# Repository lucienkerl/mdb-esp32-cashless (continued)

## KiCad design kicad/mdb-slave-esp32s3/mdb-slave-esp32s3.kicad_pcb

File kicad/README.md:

# MDB ESP32 Cashless Devices

This repository contains open hardware projects for MDB-based cashless devices built around the ESP32 platform.

## PCBWay Project Store
You can view and order the PCBs directly from PCBWay using the links below:

👉 MDB ESP32-S3-WROOM-1U board: https://www.pcbway.com/project/shareproject/MDB_Slave_ESP32_S3_WROOM_1U_4_layer_cashless_telemetry_board_for_vending_mac_cb2e3ef8.html

👉 Other boards: https://www.pcbway.com/project/member/?bmbno=1B3B95CB-4E28-4D

---

### MDB ESP32-S3-WROOM-1U Cashless Device

4-layer board with external antenna, relays and sensor I/O — see [`mdb_slave_esp32s3-wroom-1u/`](mdb_slave_esp32s3-wroom-1u/) for sources, gerbers and the interactive BOM.

### LTE add-on module (SIM7080G) for the WROOM-1U board

Plugs into the WROOM-1U board's J2 socket and adds LTE-M / NB-IoT — see [`lte-addon-sim7080g/`](lte-addon-sim7080g/).

### MDB ESP32 Cashless Device

### MDB ESP32 GPS/LTE-M/NB-IoT Cashless Device

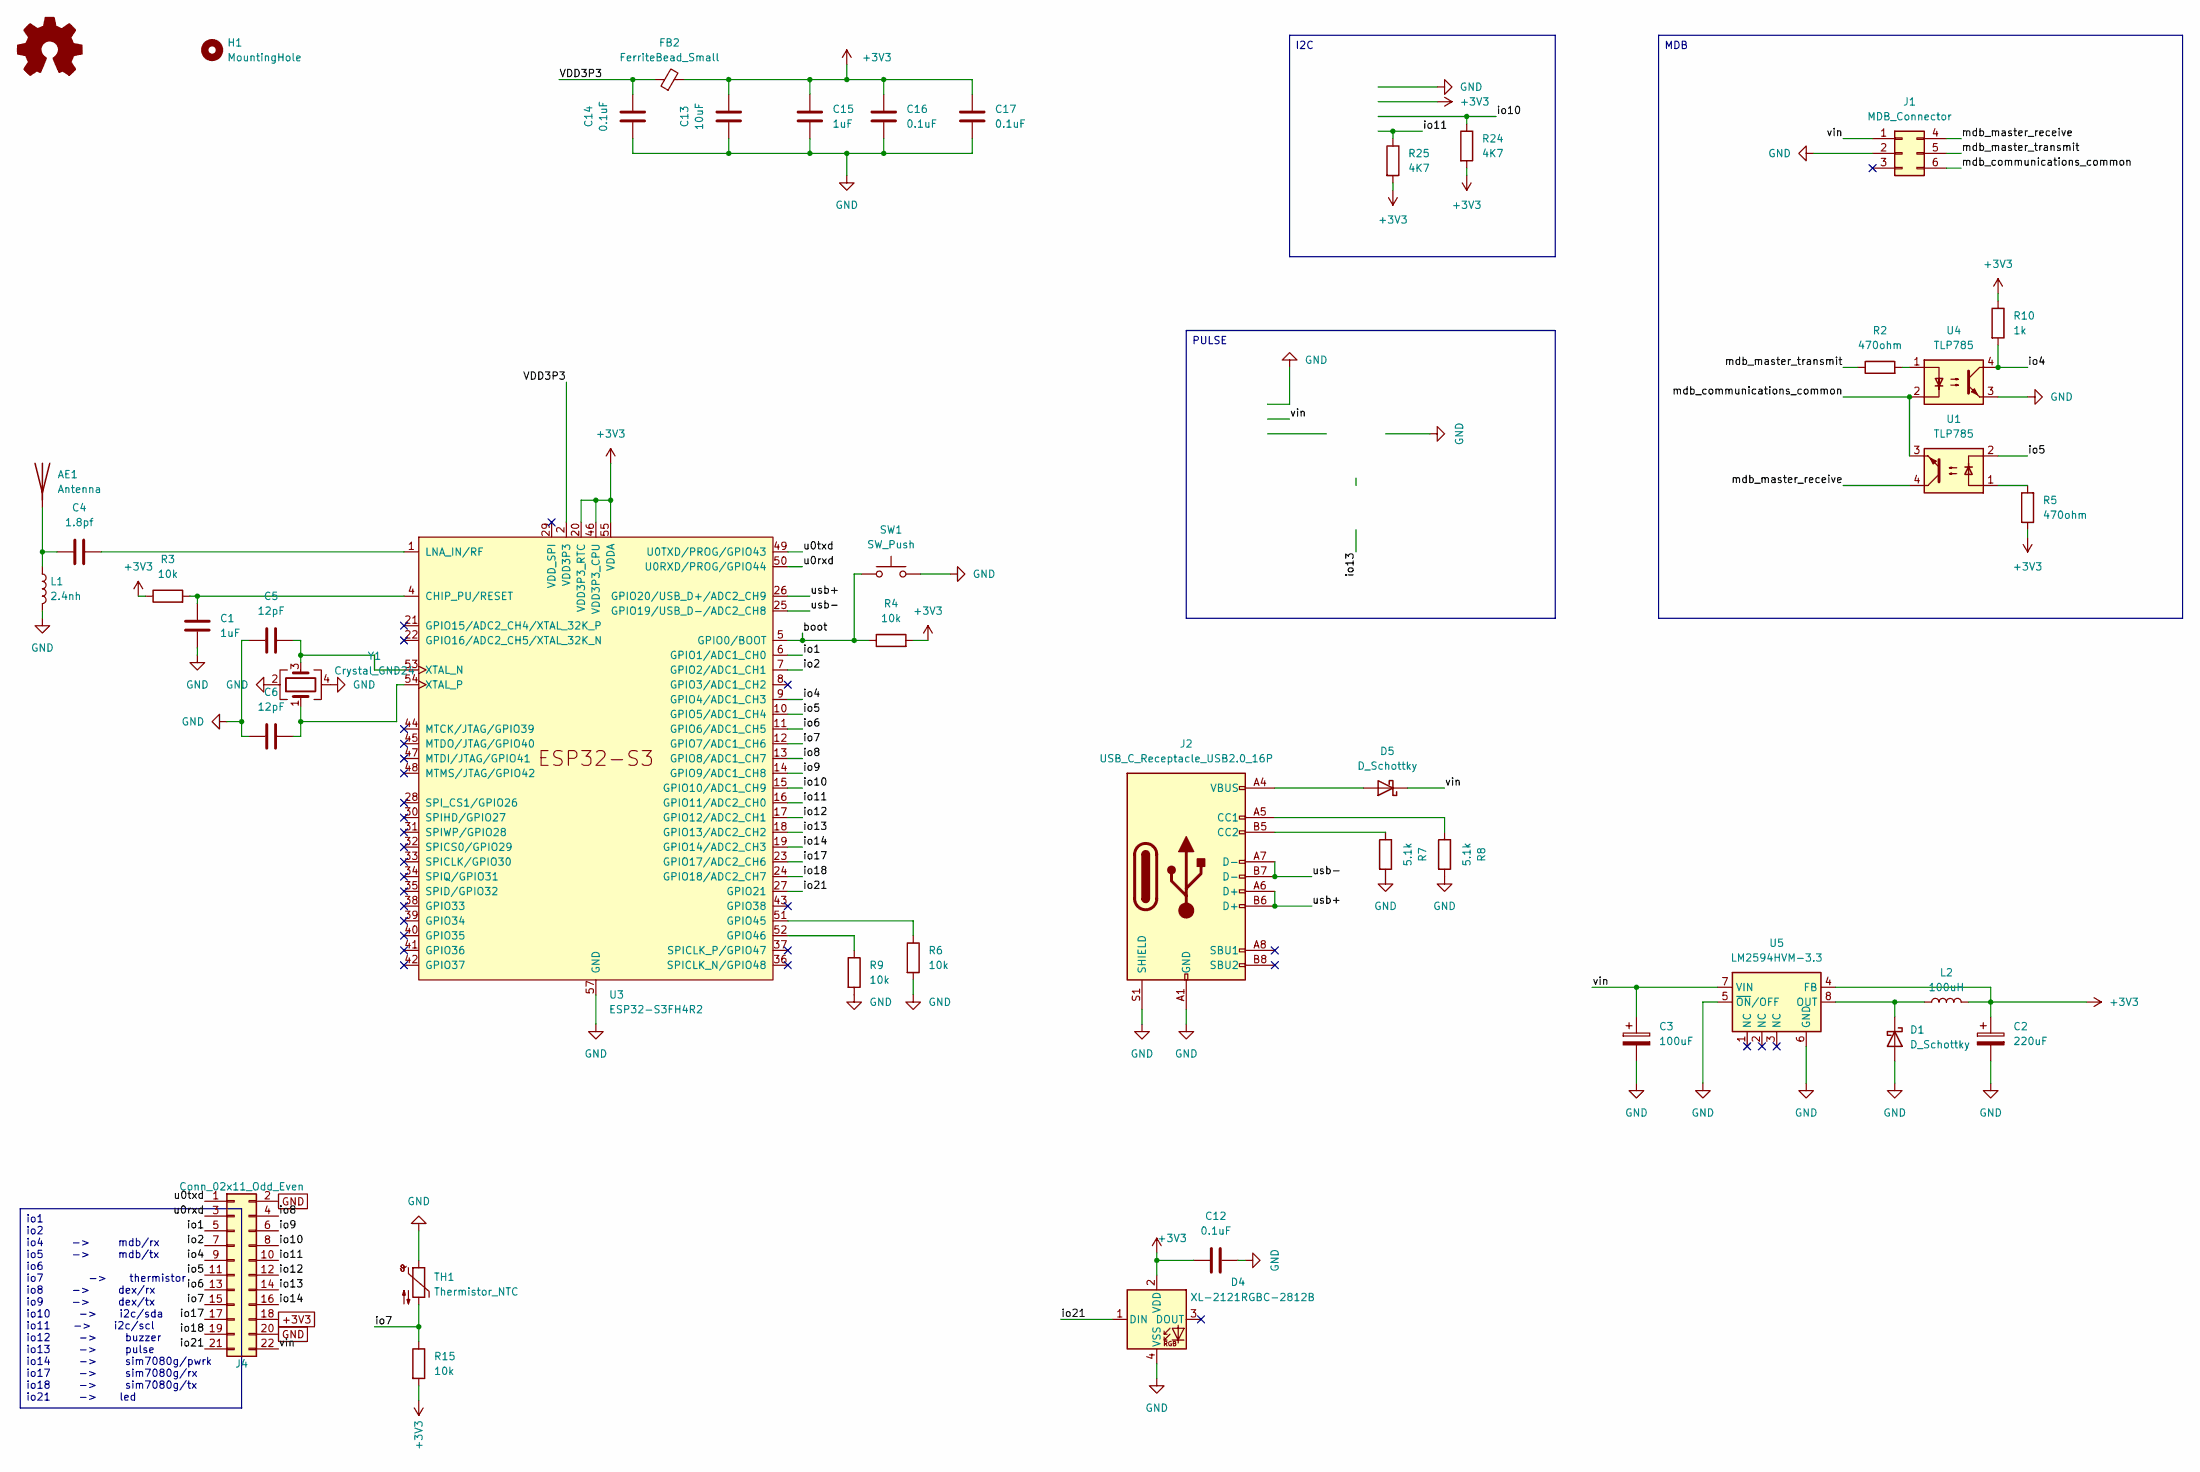
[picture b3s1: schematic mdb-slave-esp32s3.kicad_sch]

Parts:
AE1: Antenna; Texas_SWRA117D_2.4GHz_Left
C1, C15: 1uF; C_0603_1608Metric; LCSC# C6119849
C2: 220uF; CP_EIA-3528-21_Kemet-B; LCSC# C30242
C3: 100uF; CP_Elec_6.3x5.8; LCSC# C128464
C4: 1.8pf; C_0603_1608Metric; LCSC# C376773
C5, C6: 12pF; C_0603_1608Metric; LCSC# C363546
C12, C14, C16, C17: 0.1uF; C_0603_1608Metric; LCSC# C5137636
C13: 10uF; C_0603_1608Metric; LCSC# C6119864
D1, D5: D_Schottky; D_SOD-123; LCSC# C18195164
D4: XL-2121RGBC-2812B; LED_WS2812B-2020_PLCC4_2.0x2.0mm; LCSC# C5349957
FB2: FerriteBead_Small; L_0603_1608Metric; LCSC# C304319
H1: MountingHole; MountingHole_2.1mm
J1: MDB_Connector; Molex_Mini-Fit_Jr_5566-06A_2x03_P4.20mm_Vertical; LCSC# C22365701
J2: USB_C_Receptacle_USB2.0_16P; USB_C_Receptacle_G-Switch_GT-USB-7010ASV; LCSC# C2988369
J4: Conn_02x11_Odd_Even; PinHeader_2x11_P2.54mm_Vertical
L1: 2.4nh; L_0603_1608Metric; LCSC# C2042508
L2: 100uH; L_7.3x7.3_H3.5; LCSC# C182195
R2, R5: 470ohm; R_0603_1608Metric; LCSC# C114669
R3, R4, R6, R9, R15: 10k; R_0603_1608Metric; LCSC# C98220
R7, R8: 5.1k; R_0603_1608Metric; LCSC# C394543
R10: 1k; R_0603_1608Metric; LCSC# C2907113
R24, R25: 4K7; R_0603_1608Metric; LCSC# C23162
SW1: SW_Push; SW_Tactile_SPST_NO_Straight_CK_PTS636Sx25SMTRLFS; LCSC# C42435421
TH1: Thermistor_NTC; R_0603_1608Metric; LCSC# C13564
U1, U4: TLP785; SOP-4_3.8x4.1mm_P2.54mm; LCSC# C128776
U3: ESP32-S3FH4R2; QFN-56-1EP_7x7mm_P0.4mm_EP4x4mm; LCSC# C3013940
U5: LM2594HVM-3.3; SOIC-8_3.9x4.9mm_P1.27mm; LCSC# C18057294
Y1: Crystal_GND24; Crystal_SMD_3225-4Pin_3.2x2.5mm; LCSC# C7294599

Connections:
+3V3: C2.1, C12.2, C13.2, C15.2, C16.1, C17.1, D4.2 (VDD), FB2.2, J4.18, L2.2, R3.1, R4.2, R5.1, R10.1, R15.2, R24.2, R25.2, U3.20 (VDD3P3_RTC), U3.46 (VDD3P3_CPU), U3.55 (VDDA), U3.56 (VDDA), U5.4 (FB)
/boot: R4.1, SW1.1, U3.5 (GPIO0/BOOT)
/io1: J4.5, U3.6 (GPIO1/ADC1_CH0)
/io2: J4.7, U3.7 (GPIO2/ADC1_CH1)
/io4: J4.9, R10.2, U3.9 (GPIO4/ADC1_CH3), U4.4
/io5: J4.11, U1.2, U3.10 (GPIO5/ADC1_CH4)
/io6: J4.13, U3.11 (GPIO6/ADC1_CH5)
/io7: J4.15, R15.1, TH1.2, U3.12 (GPIO7/ADC1_CH6)
/io8: J4.4, U3.13 (GPIO8/ADC1_CH7)
/io9: J4.6, U3.14 (GPIO9/ADC1_CH8)
/io10: J4.8, R24.1, U3.15 (GPIO10/ADC1_CH9)
/io11: J4.10, R25.1, U3.16 (GPIO11/ADC2_CH0)
/io12: J4.12, U3.17 (GPIO12/ADC2_CH1)
/io13: J4.14, U3.18 (GPIO13/ADC2_CH2)
/io14: J4.16, U3.19 (GPIO14/ADC2_CH3)
/io17: J4.17, U3.23 (GPIO17/ADC2_CH6)
/io18: J4.19, U3.24 (GPIO18/ADC2_CH7)
/io21: D4.1 (DIN), J4.21, U3.27 (GPIO21)
/mdb_communications_common: J1.6, U1.3, U4.2
/mdb_master_receive: J1.4, U1.4
/mdb_master_transmit: J1.5, R2.1
/u0rxd: J4.3, U3.50 (U0RXD/PROG/GPIO44)
/u0txd: J4.1, U3.49 (U0TXD/PROG/GPIO43)
/usb+: J2.A6 (D+), J2.B6 (D+), U3.26 (GPIO20/USB_D+/ADC2_CH9)
/usb-: J2.A7 (D-), J2.B7 (D-), U3.25 (GPIO19/USB_D-/ADC2_CH8)
/vin: C3.1, D5.1 (K), J1.1, J4.22, U5.7 (VIN)
GND: C1.2, C2.2, C3.2, C5.1, C6.1, C12.1, C13.1, C14.1, C15.1, C16.2, C17.2, D1.2 (A), D4.4 (VSS), J1.2, J2.A1 (GND), J2.A12 (GND), J2.B1 (GND), J2.B12 (GND), J2.S1 (SHIELD), J4.2, J4.20, L1.2, R6.2, R7.2, R8.2, R9.2, SW1.2, TH1.1, U3.57 (GND), U4.3, U5.5 (~ON/OFF), U5.6 (GND), Y1.2, Y1.4
unnamed: AE1.1 (A_1), C4.1, L1.1
unnamed: D1.1 (K), L2.1, U5.8 (OUT)
unnamed: D5.2 (A), J2.A4 (VBUS), J2.A9 (VBUS), J2.B4 (VBUS), J2.B9 (VBUS)
unnamed: J2.A5 (CC1), R8.1
unnamed: J2.B5 (CC2), R7.1
unnamed: R2.2, U4.1
unnamed: R5.2, U1.1
unnamed: C1.1, R3.2, U3.4 (CHIP_PU/RESET)
unnamed: R6.1, U3.51 (GPIO45)
unnamed: R9.1, U3.52 (GPIO46)
unnamed: C4.2, U3.1 (LNA_IN/RF)
unnamed: C5.2, U3.53 (XTAL_N), Y1.3
unnamed: C6.2, U3.54 (XTAL_P), Y1.1
VDD3P3: C14.2, FB2.1, U3.2 (VDD3P3), U3.3 (VDD3P3)

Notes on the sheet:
io1 io2 io4 -> mdb/rx io5 -> mdb/tx io6 io7 -> thermistor io8 -> dex/rx io9 -> dex/tx io10 -> i2c/sda io11 -> i2c/scl io12 -> buzzer io13 -> pulse io14 -> sim7080g/pwrk io17 -> sim7080g/rx io18 -> sim7080g/tx io21 -> led
PULSE
I2C
MDB

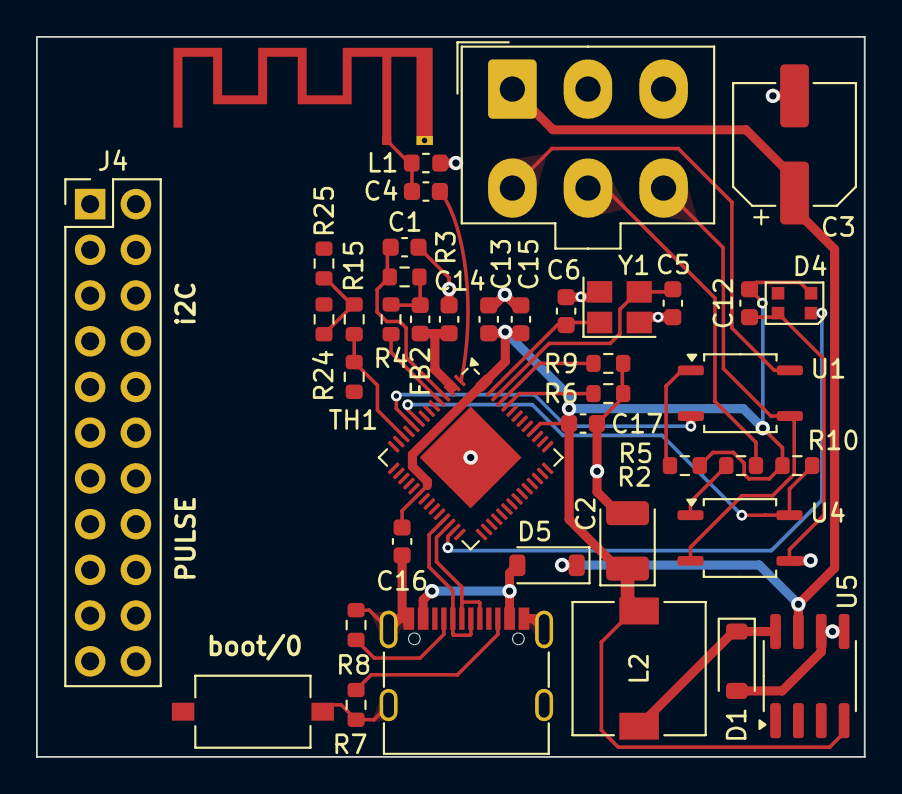
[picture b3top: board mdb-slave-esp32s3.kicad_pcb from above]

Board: 2 copper layers, 46.0 x 40.0 mm, 41 parts (0 on the bottom side), 41 nets.

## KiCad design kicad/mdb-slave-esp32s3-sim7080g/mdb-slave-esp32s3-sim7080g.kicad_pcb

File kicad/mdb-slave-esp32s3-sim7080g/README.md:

# mdb-slave-esp32s3-sim7080g — pin mapping & firmware compatibility

Custom PCB variant of `mdb-slave-esp32s3` adding an onboard SIM7080G
(GPS/LTE-M/NB-IoT) modem — see `kicad/README.md` for the board photo.

## Confirmed pin mapping (traced from `mdb-slave-esp32s3-sim7080g.kicad_pcb` netlist)

| GPIO | Net | Function |
|---|---|---|
| 4 | `/io4` | MDB bus (bridged to `/mdb_communications_common` — same role as the base board's `PIN_MDB_RX`) |
| 5 | `/io5` | MDB bus (bridged to `/mdb_communications_common` — same role as `PIN_MDB_TX`) |
| 14 | `/io14` → R (base) → Q2 | SIM7080G PWRKEY, via an inverting NPN driver (Q2: base from GPIO14 through a resistor, emitter to GND, collector to `/pwrkey`) — GPIO high → Q2 conducts → PWRKEY pulled low ("press"), same inverted-polarity convention as `MODEM_PWRKEY_INVERTED` in `modem.c` |
| 17 | `/io17` → Q1 → `/sim_uart1_rx` | ESP TX → SIM7080G UART1_RXD, via level-shift transistor Q1 |
| 18 | `/io18` → Q3 → `/sim_uart1_tx` | SIM7080G UART1_TXD → ESP RX, via level-shift transistor Q3 |

No AXP2101 (or any other PMU) is present on this board — modem power is
gated purely by the PWRKEY drive above. SIM7080G UART1 RTS/CTS/DCD/DTR/RI
are all left unconnected (2-wire UART only).

## Firmware status: supported

`main/modem.c` uses exactly this pinout by default (RX 18, TX 17, PWRKEY
14, `MODEM_PWRKEY_INVERTED` = 1) and needs no PMU. (An earlier revision of
this file described a LilyGo-devkit pinout in `modem.c`; that is gone.)

The WROOM-1U board has no modem of its own; its optional plug-in LTE module
([`../lte-addon-sim7080g/`](../lte-addon-sim7080g/)) reuses this board's
modem circuit on GPIO39/40/41 and is selected at boot via `modem_set_pins()`.

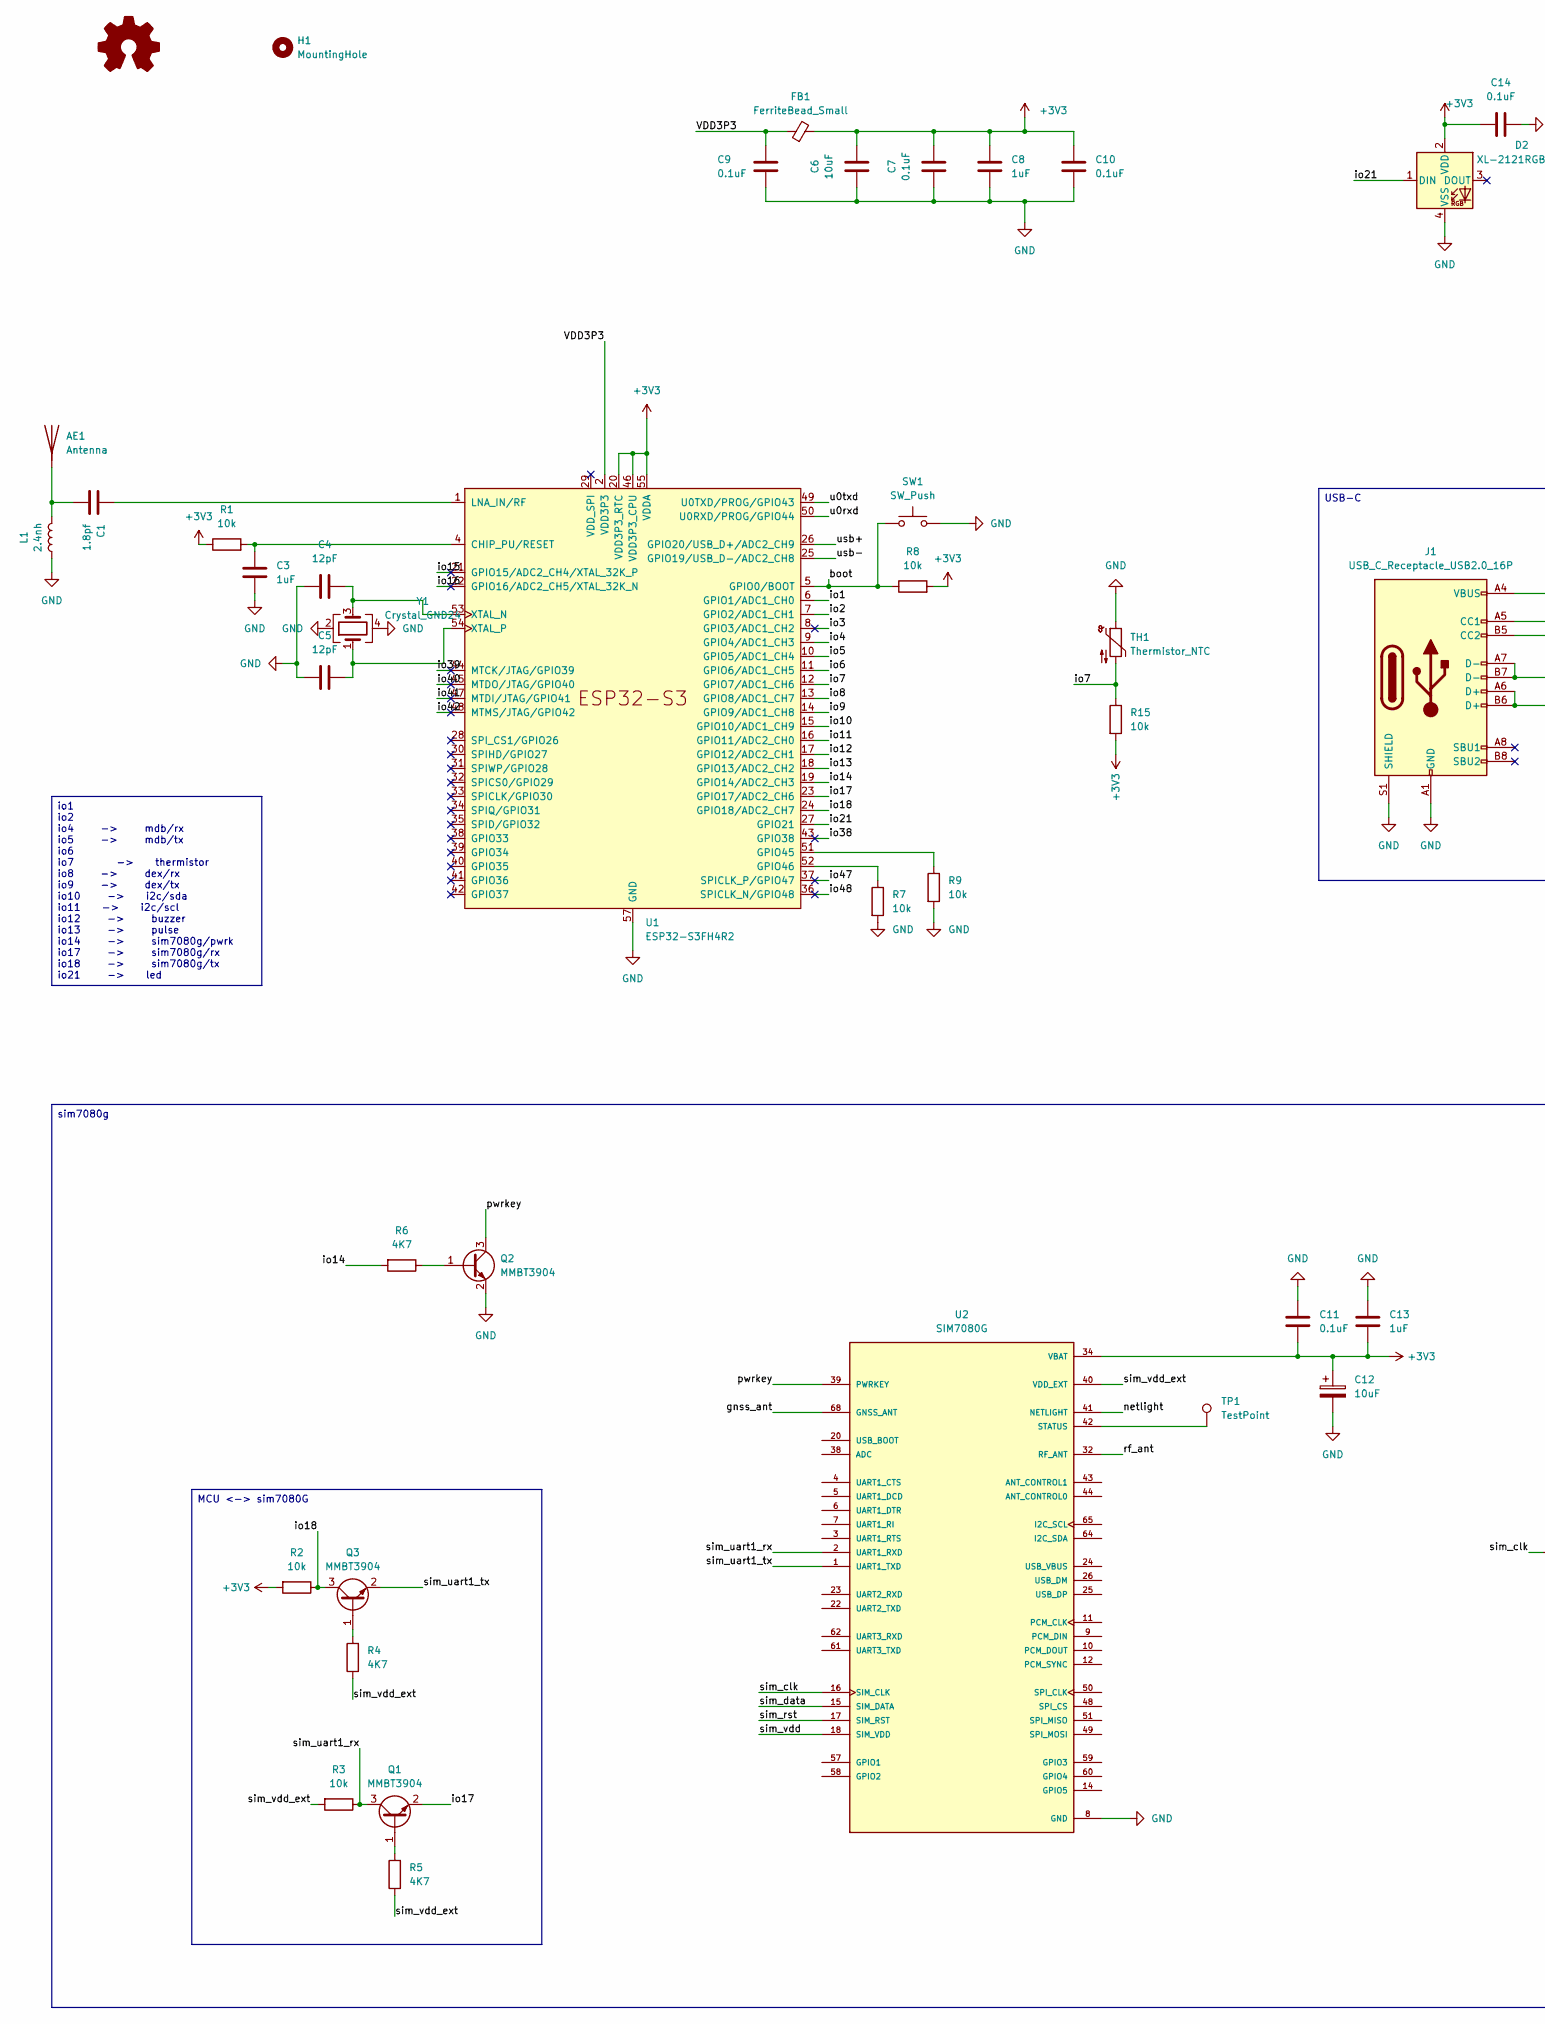
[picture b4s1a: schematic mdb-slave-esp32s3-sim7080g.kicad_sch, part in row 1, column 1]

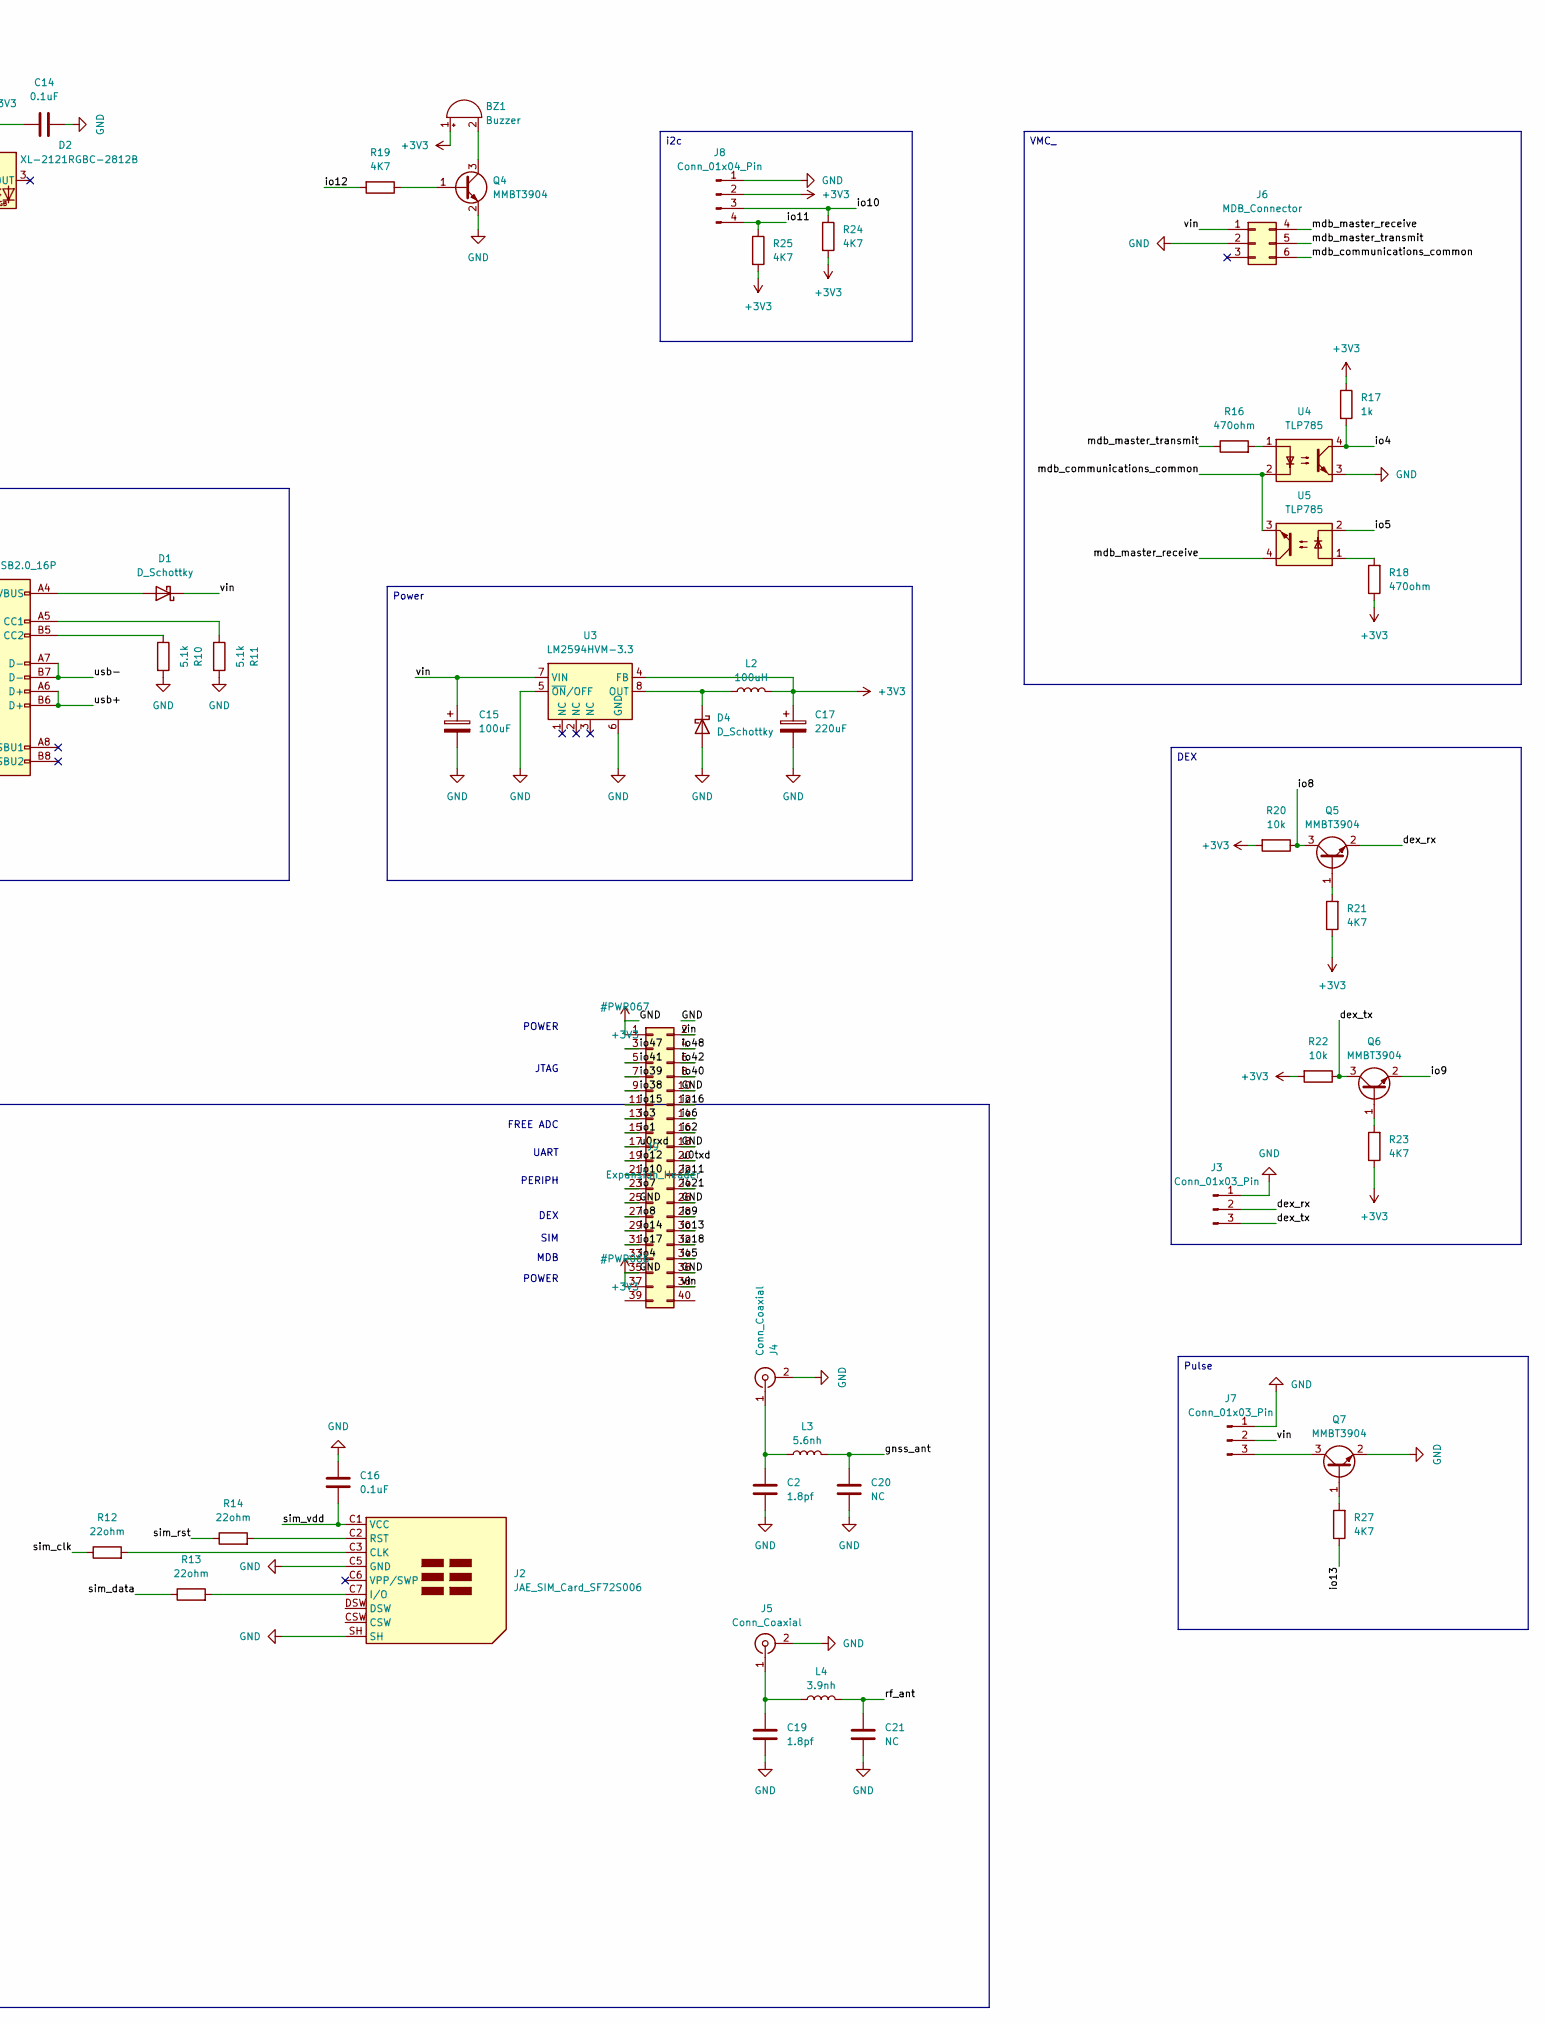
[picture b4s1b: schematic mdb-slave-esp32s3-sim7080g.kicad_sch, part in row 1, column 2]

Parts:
AE1: Antenna; Texas_SWRA117D_2.4GHz_Left
BZ1: Buzzer; Buzzer_CUI_CPT-9019S-SMT; LCSC# C255327
C1, C2, C19: 1.8pf; C_0603_1608Metric; LCSC# C376773
C3, C8, C13: 1uF; C_0603_1608Metric; LCSC# C6119849
C4, C5: 12pF; C_0603_1608Metric; LCSC# C363546
C6: 10uF; C_0603_1608Metric; LCSC# C6119864
C7, C9, C10, C11, C14, C16: 0.1uF; C_0603_1608Metric; LCSC# C5137636
C12: 10uF; CP_EIA-3528-21_Kemet-B; LCSC# C110053
C15: 100uF; CP_Elec_6.3x5.8; LCSC# C128464
C17: 220uF; CP_EIA-3528-21_Kemet-B; LCSC# C30242
C20: NC; C_0603_1608Metric; LCSC# C376773
C21: NC; C_0603_1608Metric
D1, D4: D_Schottky; D_SOD-123; LCSC# C18195164
D2: XL-2121RGBC-2812B; LED_WS2812B-2020_PLCC4_2.0x2.0mm; LCSC# C5349957
FB1: FerriteBead_Small; L_0603_1608Metric; LCSC# C304319
H1: MountingHole; MountingHole_2.1mm
J1: USB_C_Receptacle_USB2.0_16P; USB_C_Receptacle_G-Switch_GT-USB-7010ASV; LCSC# C2988369
J2: JAE_SIM_Card_SF72S006; LCSC# C2977286
J3, J7: Conn_01x03_Pin; JST_PH_B3B-PH-K_1x03_P2.00mm_Vertical; LCSC# C131339
J4, J5: Conn_Coaxial; U.FL_Hirose_U.FL-R-SMT-1_Vertical; LCSC# C88374
J6: MDB_Connector; Molex_Mini-Fit_Jr_5566-06A_2x03_P4.20mm_Vertical; LCSC# C22365701
J8: Conn_01x04_Pin; JST_PH_B4B-PH-K_1x04_P2.00mm_Vertical; LCSC# C131334
J9: Expansion_Header; PinHeader_2x20_P2.54mm_Vertical
L1: 2.4nh; L_0603_1608Metric; LCSC# C2042508
L2: 100uH; L_7.3x7.3_H3.5; LCSC# C182195
L3: 5.6nh; L_0603_1608Metric; LCSC# C6652920
L4: 3.9nh; L_0603_1608Metric; LCSC# C317982
Q1, Q2, Q3, Q4, Q5, Q6, Q7: MMBT3904; SOT-23; LCSC# C916374
R1, R2, R3, R7, R8, R9, R15, R20, R22: 10k; R_0603_1608Metric; LCSC# C98220
R4, R5, R6, R19, R21, R23, R24, R25, R27: 4K7; R_0603_1608Metric; LCSC# C23162
R10, R11: 5.1k; R_0603_1608Metric; LCSC# C394543
R12, R13, R14: 22ohm; R_0603_1608Metric; LCSC# C23345
R16, R18: 470ohm; R_0603_1608Metric; LCSC# C114669
R17: 1k; R_0603_1608Metric; LCSC# C2907113
SW1: SW_Push; SW_Tactile_SPST_NO_Straight_CK_PTS636Sx25SMTRLFS; LCSC# C42435421
TH1: Thermistor_NTC; R_0603_1608Metric; LCSC# C13564
TP1: TestPoint; TestPoint_Pad_D1.0mm
U1: ESP32-S3FH4R2; QFN-56-1EP_7x7mm_P0.4mm_EP4x4mm; LCSC# C3013940
U2: SIM7080G; XCVR_SIM7080G; PARTREV 1.04; LCSC# C2943992
U3: LM2594HVM-3.3; SOIC-8_3.9x4.9mm_P1.27mm; LCSC# C18057294
U4, U5: TLP785; SOP-4_3.8x4.1mm_P2.54mm; LCSC# C128776
Y1: Crystal_GND24; Crystal_SMD_3225-4Pin_3.2x2.5mm; LCSC# C7294599

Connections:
+3V3: BZ1.1 (+), C2.1, C3.2, C4.1, C5.1, C6.1, C6.2, C7.1, C7.2, C8.1, C8.2, C9.2, C10.1, C10.2, C11.1, C11.2, C12.1, C12.2, C13.1, C13.2, C14.1, C14.2, C15.2, C16.2, C17.1, C17.2, C19.1, C20.1, C21.1, D2.2 (VDD), D2.4 (VSS), D4.2 (A), FB1.2, J1.A1 (GND), J1.A12 (GND), J1.B1 (GND), J1.B12 (GND), J1.S1 (SHIELD), J2.C5 (GND), J2.SH, J3.1, J4.2 (Ext), J5.2 (Ext), J6.2, J7.1, J8.1, J8.2, J9.1, J9.10, J9.18, J9.25, J9.26, J9.35, J9.36, J9.37, L1.1, L2.2, Q2.2 (E), Q4.2 (E), Q7.2 (E), R1.1, R2.2, R7.2, R8.2, R9.2, R10.2, R11.2, R15.2, R17.1, R18.1, R20.2, R21.1, R22.2, R23.1, R24.2, R25.2, SW1.2, TH1.1, U1.20 (VDD3P3_RTC), U1.46 (VDD3P3_CPU), U1.55 (VDDA), U1.56 (VDDA), U1.57 (GND), U2.8 (GND), U2.13 (GND), U2.19 (GND), U2.21 (GND), U2.27 (GND), U2.30 (GND), U2.31 (GND), U2.33 (GND), U2.34 (VBAT), U2.35 (VBAT), U2.36 (GND), U2.37 (GND), U2.45 (GND), U2.63 (GND), U2.66 (GND), U2.67 (GND), U2.69 (GND), U2.70 (GND), U2.71 (GND), U2.72 (GND), U2.73 (GND), U2.74 (GND), U2.75 (GND), U2.76 (GND), U2.77 (GND), U3.4 (FB), U3.5 (~ON/OFF), U3.6 (GND), U4.3, Y1.2, Y1.4
/boot: R8.1, SW1.1, U1.5 (GPIO0/BOOT)
/dex_rx: J3.2, Q5.2 (E)
/dex_tx: J3.3, Q6.3 (C), R22.1
/gnss_ant: C20.2, L3.2, U2.68 (GNSS_ANT)
/io1: J9.15, U1.6 (GPIO1/ADC1_CH0)
/io2: J9.16, U1.7 (GPIO2/ADC1_CH1)
/io3: J9.13, U1.8 (GPIO3/ADC1_CH2)
/io4: J9.33, R17.2, U1.9 (GPIO4/ADC1_CH3), U4.4
/io5: J9.34, U1.10 (GPIO5/ADC1_CH4), U5.2
/io6: J9.14, U1.11 (GPIO6/ADC1_CH5)
/io7: J9.23, R15.1, TH1.2, U1.12 (GPIO7/ADC1_CH6)
/io8: J9.27, Q5.3 (C), R20.1, U1.13 (GPIO8/ADC1_CH7)
/io9: J9.28, Q6.2 (E), U1.14 (GPIO9/ADC1_CH8)
/io10: J8.3, J9.21, R24.1, U1.15 (GPIO10/ADC1_CH9)
/io11: J8.4, J9.22, R25.1, U1.16 (GPIO11/ADC2_CH0)
/io12: J9.19, R19.2, U1.17 (GPIO12/ADC2_CH1)
/io13: J9.30, R27.1, U1.18 (GPIO13/ADC2_CH2)
/io14: J9.29, R6.2, U1.19 (GPIO14/ADC2_CH3)
/io15: J9.11, U1.21 (GPIO15/ADC2_CH4/XTAL_32K_P)
/io16: J9.12, U1.22 (GPIO16/ADC2_CH5/XTAL_32K_N)
/io17: J9.31, Q1.2 (E), U1.23 (GPIO17/ADC2_CH6)
/io18: J9.32, Q3.3 (C), R2.1, U1.24 (GPIO18/ADC2_CH7)
/io21: D2.1 (DIN), J9.24, U1.27 (GPIO21)
/io38: J9.9, U1.43 (GPIO38)
/io39: J9.7, U1.44 (MTCK/JTAG/GPIO39)
/io40: J9.8, U1.45 (MTDO/JTAG/GPIO40)
/io41: J9.5, U1.47 (MTDI/JTAG/GPIO41)
/io42: J9.6, U1.48 (MTMS/JTAG/GPIO42)
/io47: J9.3, U1.37 (SPICLK_P/GPIO47)
/io48: J9.4, U1.36 (SPICLK_N/GPIO48)
/mdb_communications_common: J6.6, U4.2, U5.3
/mdb_master_receive: J6.4, U5.4
/mdb_master_transmit: J6.5, R16.1
/netlight: U2.41 (NETLIGHT)
/pwrkey: Q2.3 (C), U2.39 (PWRKEY)
/rf_ant: C21.2, L4.2, U2.32 (RF_ANT)
/sim_clk: R12.1, U2.16 (SIM_CLK)
/sim_data: R13.1, U2.15 (SIM_DATA)
/sim_rst: R14.1, U2.17 (SIM_RST)
/sim_uart1_rx: Q1.3 (C), R3.1, U2.2 (UART1_RXD)
/sim_uart1_tx: Q3.2 (E), U2.1 (UART1_TXD)
/sim_vdd: C16.1, J2.C1 (VCC), U2.18 (SIM_VDD)
/sim_vdd_ext: R3.2, R4.1, R5.1, U2.40 (VDD_EXT)
/u0rxd: J9.17, U1.50 (U0RXD/PROG/GPIO44)
/u0txd: J9.20, U1.49 (U0TXD/PROG/GPIO43)
/usb+: J1.A6 (D+), J1.B6 (D+), U1.26 (GPIO20/USB_D+/ADC2_CH9)
/usb-: J1.A7 (D-), J1.B7 (D-), U1.25 (GPIO19/USB_D-/ADC2_CH8)
/vin: C15.1, D1.1 (K), J6.1, J7.2, J9.2, J9.38, U3.7 (VIN)
unnamed: AE1.1 (A_1), C1.1, L1.2
unnamed: BZ1.2 (-), Q4.3 (C)
unnamed: D1.2 (A), J1.A4 (VBUS), J1.A9 (VBUS), J1.B4 (VBUS), J1.B9 (VBUS)
unnamed: D4.1 (K), L2.1, U3.8 (OUT)
unnamed: J1.A5 (CC1), R11.1
unnamed: J1.B5 (CC2), R10.1
unnamed: J2.C3 (CLK), R12.2
unnamed: J2.C7 (I/O), R13.2
unnamed: J2.C2 (RST), R14.2
unnamed: C2.2, J4.1 (In), L3.1
unnamed: C19.2, J5.1 (In), L4.1
unnamed: J7.3, Q7.3 (C)
unnamed: Q1.1 (B), R5.2
unnamed: Q2.1 (B), R6.1
unnamed: Q3.1 (B), R4.2
unnamed: Q4.1 (B), R19.1
unnamed: Q5.1 (B), R21.2
unnamed: Q6.1 (B), R23.2
unnamed: Q7.1 (B), R27.2
unnamed: R16.2, U4.1
unnamed: R18.2, U5.1
unnamed: C3.1, R1.2, U1.4 (CHIP_PU/RESET)
unnamed: R9.1, U1.51 (GPIO45)
unnamed: R7.1, U1.52 (GPIO46)
unnamed: C1.2, U1.1 (LNA_IN/RF)
unnamed: C4.2, U1.53 (XTAL_N), Y1.3
unnamed: C5.2, U1.54 (XTAL_P), Y1.1
unnamed: TP1.1 (1_1), U2.42 (STATUS)
VDD3P3: C9.1, FB1.1, U1.2 (VDD3P3), U1.3 (VDD3P3)

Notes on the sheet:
sim7080g
Power
USB-C
Pulse
MCU <-> sim7080G
io1 io2 io4 -> mdb/rx io5 -> mdb/tx io6 io7 -> thermistor io8 -> dex/rx io9 -> dex/tx io10 -> i2c/sda io11 -> i2c/scl io12 -> buzzer io13 -> pulse io14 -> sim7080g/pwrk io17 -> sim7080g/rx io18 -> sim7080g/tx io21 -> led
DEX
i2c
VMC_
POWER
MDB
SIM
PERIPH
UART
FREE ADC
JTAG

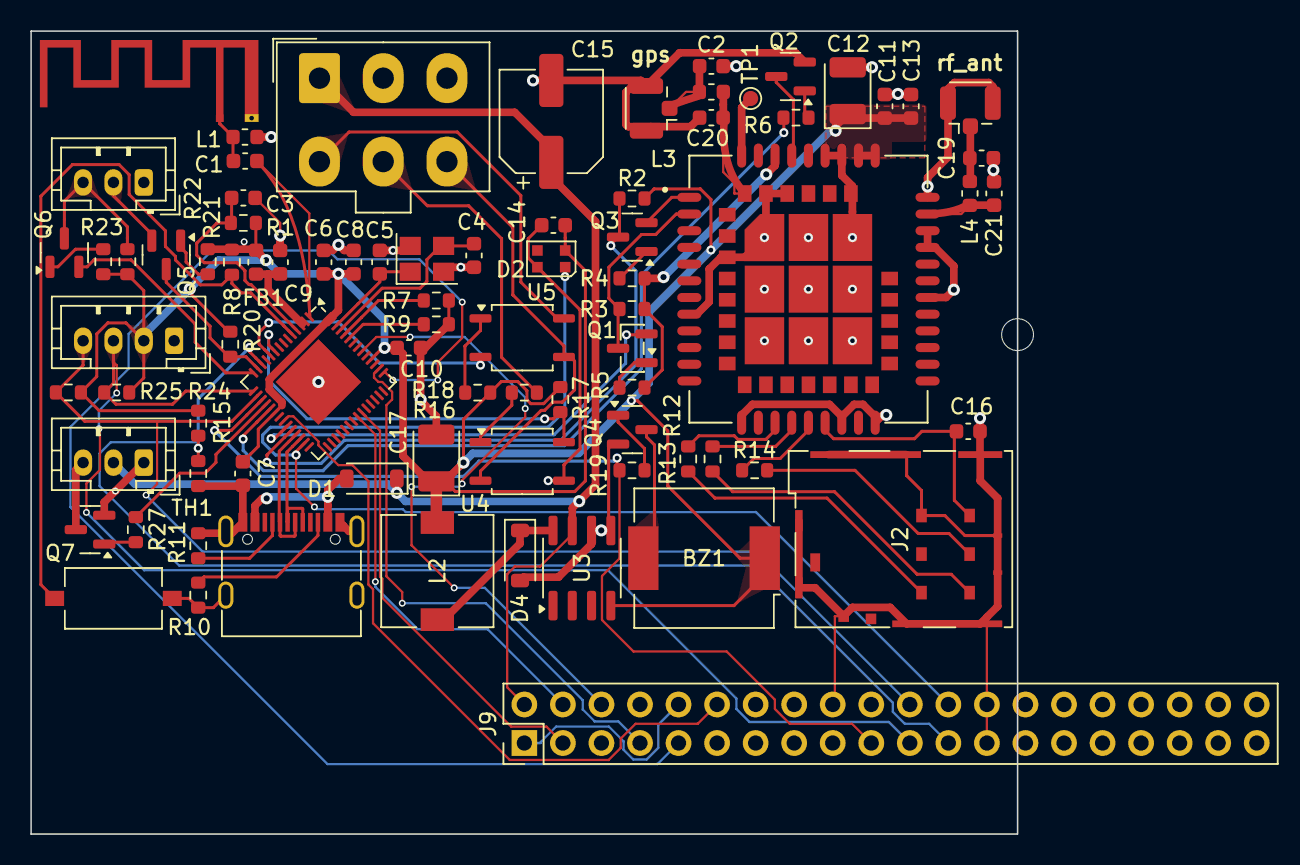
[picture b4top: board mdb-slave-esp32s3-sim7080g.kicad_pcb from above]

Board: 2 copper layers, 65.0 x 52.9 mm, 82 parts (0 on the bottom side), 77 nets.

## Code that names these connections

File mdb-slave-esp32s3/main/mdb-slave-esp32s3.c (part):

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#define PIN_MDB_RX              GPIO_NUM_4
#define PIN_MDB_TX              GPIO_NUM_5
#define PIN_MDB_LED             GPIO_NUM_21
#define PIN_DEX_RX              GPIO_NUM_8
#define PIN_DEX_TX              GPIO_NUM_9
#define PIN_BUZZER_PWR          GPIO_NUM_12

/* WROOM-1U's buzzer is an MLT-8530 electro-magnetic transducer — per its
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 * vend credit. */
#define PIN_PULSE_1             GPIO_NUM_13

/* Custom digital inputs (J11/J13/J14 on the WROOM-1U board). GPIO6 was
 * already clear of both boards' PIN_* usage. custom_input2/3 moved from
 * GPIO47/48 to GPIO17/18 per the latest WROOM-1U PCB revision — safe on
 * this board specifically because it's WiFi-only (no SIM7080G populated,
 * so there's nothing on this PCB using PIN_SIM7080G_TX/RX). GPIO46/47/48
 * are free on this revision and unused. */
#define PIN_CUSTOM_INPUT1       GPIO_NUM_6
#define PIN_CUSTOM_INPUT2       GPIO_NUM_17
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#define PIN_ONEWIRE_1           GPIO_NUM_15
#define PIN_ONEWIRE_2           GPIO_NUM_16

/* Board-ID strap: GPIO3 is unused on both the original mdb-slave-esp32s3
 * PCB and this WROOM-1U PCB per their schematics. Fitting a 10k pull-down
 * to GND on GPIO3 on the WROOM-1U board only (nothing to add on the
 * original board — its floating pin reads HIGH via the internal pull-up
 * below) lets a single firmware image tell the two boards apart at boot,
 * instead of relying on whoever flashes it picking the right binary. */
#define PIN_BOARD_ID            GPIO_NUM_3

/* LTE add-on module (SIM7080G) on the WROOM-1U's J2 socket — see
 * kicad/lte-addon-sim7080g. J2 pin 1..4 = GPIO42..39. The module pulls
 * DETECT up to 3V3 (10k); without it the internal pull-down reads LOW. */
#define PIN_LTE_ADDON_DETECT    GPIO_NUM_42
#define PIN_LTE_ADDON_PWRKEY    GPIO_NUM_41   /* high = PWRKEY pressed */
#define PIN_LTE_ADDON_TX        GPIO_NUM_40   /* ESP TX -> modem RXD */
#define PIN_LTE_ADDON_RX        GPIO_NUM_39   /* modem TXD -> ESP RX */

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    }
}

// True on the WROOM-1U PCB (external 10k pull-down fitted on GPIO3),
// false on the original mdb-slave-esp32s3 PCB (GPIO3 floats, so the
// internal pull-up wins and it reads HIGH). See PIN_BOARD_ID above.
static bool detect_board_variant(void) {
    gpio_config_t id_cfg = {
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}

// WROOM-1U only: true when the LTE add-on module sits on J2 (its 10k pulls
// GPIO42 above the internal pull-down). See PIN_LTE_ADDON_DETECT above.
static bool detect_lte_addon(void) {
    gpio_config_t cfg = {
        .pin_bit_mask = (1ULL << PIN_LTE_ADDON_DETECT),
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    mqtt_publish_safe(mqttClient, topic, msg, 0, 1, 0);
}

/* Unused when the RFID reader claims GPIO13 (the default), see app_main. */
static __attribute__((unused)) void pulse_input_task(void *arg) {
    pcnt_unit_config_t unit_config = {
        .low_limit  = -1,
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	gpio_set_direction(PIN_MDB_TX, GPIO_MODE_INPUT);  // idle: high-Z (tri-state)

	/* GPIO 12 = PIN_BUZZER_PWR on the production PCB (drives a buzzer).
	 * The SIM7080G's PWRKEY sits on its own pin (modem.c's
	 * MODEM_PIN_PWR, GPIO 14) and its main power comes straight off the
	 * board's regulator, so this LOW init doesn't affect cellular
	 * bring-up. */
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
	//------------- Relay / custom inputs / 1-Wire (WROOM-1U) --------------//
	//----------------------------------------------------------------------//
	// All three are unwired on the original board (GPIO1/2/6/15/16/17/18
	// are unused there) — only touch them when detect_board_variant()
	// found the WROOM-1U pull-down, same gating as the DEX/UART1 block
	// below.
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
	//---------------- UART1 - EVA DTS DEX/DDCMP ---------------//
	//----------------------------------------------------------//
	// GPIO8/9 (PIN_DEX_RX/TX) carry DEX telemetry only on the original
	// board. WROOM-1U has no DEX reader hardware at all — GPIO8/9 are
	// simply free/unused on that board — so this whole block is skipped
	// when detect_board_variant() found the WROOM-1U pull-down.
	if (!board_is_wroom_1u) {
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				.flow_ctrl = UART_HW_FLOWCTRL_DISABLE };

		uart_param_config(UART_NUM_1, &uart_config_1);
		uart_set_pin( UART_NUM_1, PIN_DEX_TX, PIN_DEX_RX, -1, -1);
		uart_driver_install(UART_NUM_1, 256, 256, 0, NULL, 0);

		// ---
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
	//---------------- Pulse input (J8, original board only) ---------------//
	//----------------------------------------------------------------------//
	// GPIO13 was desoldered on the WROOM-1U PCB revision — nothing to read
	// there. Same gating as the DEX/UART1 block above.
	// The serial RFID reader (rfid_reader.c) also listens on GPIO13 by
	// default; PCNT would count its UART frames as pulses, so the pulse
	// task stays off whenever the reader claims the same pin.
#if CONFIG_RFID_READER_ENABLE && (CONFIG_RFID_RX_GPIO == 13)
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	 * and calls esp_wifi_start(). Once IP_EVENT_STA_GOT_IP fires, the
	 * UPLINK_UP callback above starts MQTT/SNTP/watchdog. */
	/* WROOM-1U has no modem of its own. The optional LTE module on J2
	 * (kicad/lte-addon-sim7080g) pulls GPIO42 high and talks on
	 * GPIO39/40/41; without it the probe stays off, because the default
	 * modem pins GPIO17/18 are custom inputs 2/3 on this board. */
	if (g_board_is_wroom_1u) {
		if (detect_lte_addon()) {
			modem_set_pins(PIN_LTE_ADDON_RX, PIN_LTE_ADDON_TX, PIN_LTE_ADDON_PWRKEY);
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
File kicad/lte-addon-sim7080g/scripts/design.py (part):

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mainboard's J2 socket and the outline can be checked against the parts below.

Mainboard J2 (1x6 socket, rev 1.4.1):
  1 MTMS = GPIO42   2 MTDI = GPIO41   3 MTDO = GPIO40   4 MTCK = GPIO39
  5 GND             6 +3V3

Supply: the modem runs from the mainboard's 3V3 rail through J2, like on the
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PROJECT = "lte-addon-sim7080g"

# GPIO roles (firmware: modem.c / mdb-slave-esp32s3.c)
#   GPIO40 ESP TX  -> modem UART1_RXD (via level shifter Q1)
#   GPIO39 ESP RX  <- modem UART1_TXD (via level shifter Q2)
#   GPIO41 PWRKEY  -> Q3 pulls PWRKEY low (GPIO high = "press", same
#                     polarity as MODEM_PWRKEY_INVERTED=1)
#   GPIO42 DETECT  <- R8 pulls it up to 3V3: HIGH when the module is plugged
#                     in, LOW (internal pull-down) when it is not

GND_PINS_U2 = ["8", "13", "19", "21", "27", "30", "31", "33", "36", "37", "45",
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     {"1": "PWRKEY_CTL", "2": "Q3_B"}, {}),
    ("R7", "Device:R", "4.7k", "Resistor_SMD:R_0603_1608Metric",
     {"1": "Q3_B", "2": "GND"},
     {"note": "Keeps Q3 off against a weak pull-up on GPIO41 during ESP reset."}),

    # --- module detect --------------------------------------------------------
    ("R8", "Device:R", "10k", "Resistor_SMD:R_0603_1608Metric",
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    ("Modem supply (from the mainboard 3V3)", ["R1", "C1", "C2", "C3", "C4", "C5", "C6", "#FLG03"]),
    ("SIM7080G", ["U1"]),
    ("UART level shifters 3.3 V <-> 1.8 V", ["Q1", "R2", "R3", "Q2", "R4", "R5"]),
    ("PWRKEY (GPIO41 high = key pressed)", ["Q3", "R6", "R7"]),
    ("Network LED", ["Q4", "R9", "R10", "R11", "D1"]),
    ("Nano-SIM", ["J2", "R12", "R13", "R14", "C7"]),
    ("LTE antenna", ["R15", "C8", "C9", "J3"]),
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
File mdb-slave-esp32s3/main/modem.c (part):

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#define NVS_KEY_MODE    "lte_mode"

/* Leonardo's custom mdb-slave-esp32s3-sim7080g PCB, confirmed against the
 * KiCad schematic (kicad/mdb-slave-esp32s3-sim7080g/) 2026-09-14: GPIO17
 * -> R3 -> U2 pin2 (UART1_RXD), GPIO18 -> R2 -> U2 pin1 (UART1_TXD), GPIO14
 * -> R6 -> Q2 (inverting transistor) -> U2 pin39 (PWRKEY).
 *
 * A short-lived LilyGo T-SIM7080G-S3 devboard used GPIO 4/5/41 instead
 * (no longer in use — production is Leonardo's PCB). Those pins also
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 * this board has its own MDB UART pins separate from the modem's. */
/* Defaults are Leonardo's SIM7080G board. The WROOM-1U board has no modem
 * of its own; the plug-in LTE module on its J2 (kicad/lte-addon-sim7080g)
 * uses GPIO39/40/41 instead and is selected with modem_set_pins() before
 * network_init(). Same PWRKEY polarity on both. */
static gpio_num_t s_pin_rx  = GPIO_NUM_18;   /* SIM7080G TX → ESP RX */
static gpio_num_t s_pin_tx  = GPIO_NUM_17;   /* ESP TX → SIM7080G RX */
static gpio_num_t s_pin_pwr = GPIO_NUM_14;   /* PWRKEY via inverting transistor */
#define MODEM_PIN_RX    s_pin_rx
#define MODEM_PIN_TX    s_pin_tx
#define MODEM_PIN_PWR   s_pin_pwr
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#define MODEM_BAUD      115200

/* PWRKEY polarity: true if the board uses an inverting transistor between
 * the ESP GPIO and the SIM7080G PWRKEY pin (GPIO high → transistor
 * conducts → PWRKEY low = "press"). false if wired direct.
 *
 * Leonardo's PCB drives PWRKEY through Q2, wired the same way as the
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    vTaskDelete(NULL);
}

void modem_set_pins(int rx, int tx, int pwrkey) {
    s_pin_rx  = (gpio_num_t)rx;
    s_pin_tx  = (gpio_num_t)tx;
    s_pin_pwr = (gpio_num_t)pwrkey;
    ESP_LOGI(TAG, "modem pins: RX=%d TX=%d PWRKEY=%d", rx, tx, pwrkey);
}

bool modem_probe(void) {
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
